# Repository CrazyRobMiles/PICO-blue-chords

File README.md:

# PICO-blue-chords

This is a chord keyboard that uses the MicroWriter chord system. It uses the Bluetooth to connect and runs on a Raspberry Pi PICO-W. It is described in the HackSpace magazine. 
## Note
This is a work in progress. The software works correctly and the PCB and the case designs are now complete but these updated designs have not been constructed. The author knows of no reason why they won't work, but he didn't know of any reasons why the prototype wouldn't work until he tried to use it...

## Using a chord keyboard
You can find instructions on how to use the keyboard and the chord shapes in the doc folder. 
## Installing the software on your PICO from the UF2 Images
You can install the software by following these steps:
1. Press down the boot button on your PICO-W.
2. Connect your PICO-W to a usb port on your computer. 
3. The PICO-W should show up as a external drive.
4. The UF2 folder holds images for left and right handed use. Drag the left or right handed uf2 file onto the drive. 
5. The PICO-W will reboot running the software.
## Printed Circuit Board Designs

The PCB designs are in the folder PICO-blue-chords-pcb. This folder also contains the partsdump.py file which can be used to extract the footprint positions for use in the case design software.
## Case 
To create a custom case design you use the PICO-blue-chords-case-builder.FCMacro macro which is in the cases folder. Load this into FreeCAD and select left or right handed and the specific key positions. The macro contains the following statements:
```
# right handed flag
right_handed = True 
if right_handed:
	keyHoles = [Little_5,Ring_5, Middle_2, Index_1, Thumb_1,Control_2]
	displayHole = Brd2
else:
      keyHoles = [Little_3,Ring_2, Middle_1, Index_2, Thumb_5,Control_5]
      displayHole = Brd1
```
Set the value of right_handed to False if you want a left-handed keyboard. Change the numbers for each key to match the position that you want for that key hole. The higher the number the farther down the keyboard the key hole will be placed. You can see the key numbers on the PCB design above. Run the macro and then export the resulting design as an STL file for printing. 
## Building the code
You use CMAKE to build the application from source. If you load the project with Visual Studio Code, make sure that you have the CMake Tools extension installed. The file CMakeLists.txt is used to create the makefiles for the build. Line 10 of this file sets the path to the SDK:
```
set(PICO_SDK_PATH "C:/Program Files/Raspberry Pi/Pico SDK v1.5.1/pico-sdk")
```
This works on my Windows system. You may need to change this when building the software on your machine. Note that you don't need to build the software yourself to use it. You can just install the image files which will be in the build folder which is created by the build process. 

## Origins

The keyboard is based on the Cykey chord design by Cy Enfield which was used as the basis of the Microwriter and Microwriter AgendA devices developed by him and Chris Rainey. You can find out more about these devices [here](http://www.computinghistory.org.uk/det/5794/Microwriter-MW4/), [here](https://www.microsoft.com/buxtoncollection/detail.aspx?id=5) and [here](https://mindmachine.co.uk/book/A/Inp-Outp/Microwriter01.html). 

If you want to buy an official Microwriter keyboard you can get one [here](https://sites.google.com/site/cykeybellaire/home). 

Have fun!

Rob Miles: [blog](https://www.robmiles.com)

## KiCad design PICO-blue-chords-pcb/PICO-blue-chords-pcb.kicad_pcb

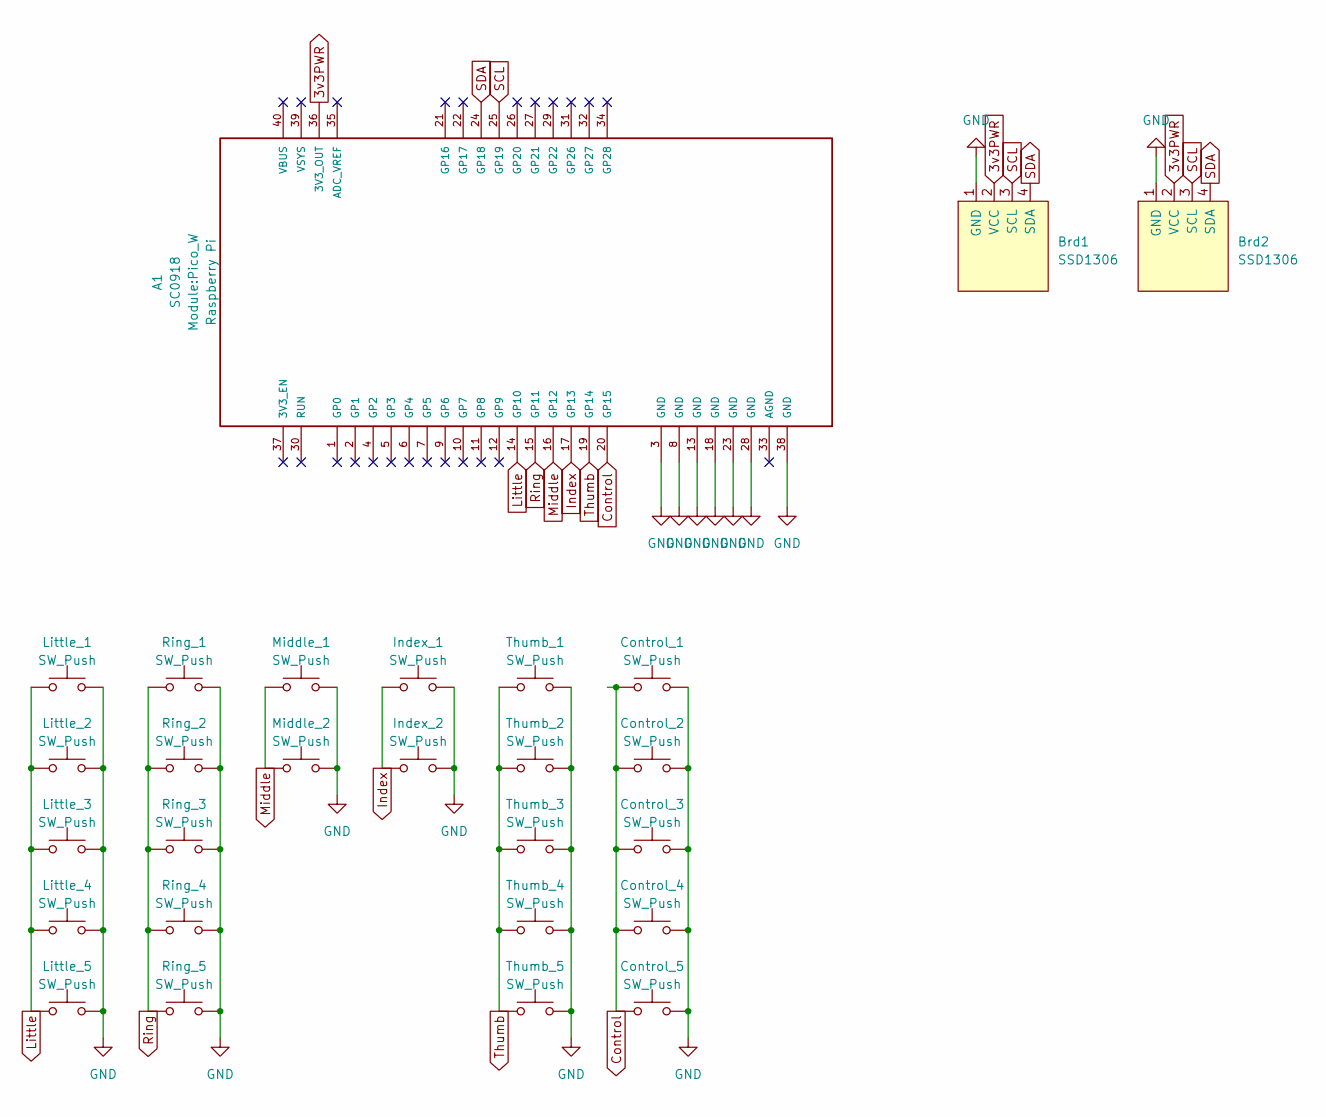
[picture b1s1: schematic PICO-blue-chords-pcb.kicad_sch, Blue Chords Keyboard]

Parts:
A1: SC0918; Pico_W; PARTREV 1.6
Brd1, Brd2: SSD1306; 128x64OLED
Control_1, Control_2, Control_3, Control_4, Control_5: SW_Push; SW_Hotswap_Kailh_MX
Index_1, Index_2: SW_Push; SW_Hotswap_Kailh_MX
Little_1, Little_2, Little_3, Little_4, Little_5: SW_Push; SW_Hotswap_Kailh_MX
Middle_1, Middle_2: SW_Push; SW_Hotswap_Kailh_MX
Ring_1, Ring_2, Ring_3, Ring_4, Ring_5: SW_Push; SW_Hotswap_Kailh_MX
Thumb_1, Thumb_2, Thumb_3, Thumb_4, Thumb_5: SW_Push; SW_Hotswap_Kailh_MX

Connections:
3v3PWR: A1.36 (3V3_OUT), Brd1.2 (VCC), Brd2.2 (VCC)
Control: A1.20 (GP15), Control_1.1, Control_2.1, Control_3.1, Control_4.1, Control_5.1
GND: A1.3 (GND), A1.8 (GND), A1.13 (GND), A1.18 (GND), A1.23 (GND), A1.28 (GND), A1.38 (GND), Brd1.1 (GND), Brd2.1 (GND), Control_1.2, Control_2.2, Control_3.2, Control_4.2, Control_5.2, Index_1.2, Index_2.2, Little_1.2, Little_2.2, Little_3.2, Little_4.2, Little_5.2, Middle_1.2, Middle_2.2, Ring_1.2, Ring_2.2, Ring_3.2, Ring_4.2, Ring_5.2, Thumb_1.2, Thumb_2.2, Thumb_3.2, Thumb_4.2, Thumb_5.2
Index: A1.17 (GP13), Index_1.1, Index_2.1
Little: A1.14 (GP10), Little_1.1, Little_2.1, Little_3.1, Little_4.1, Little_5.1
Middle: A1.16 (GP12), Middle_1.1, Middle_2.1
Ring: A1.15 (GP11), Ring_1.1, Ring_2.1, Ring_3.1, Ring_4.1, Ring_5.1
SCL: A1.25 (GP19), Brd1.3 (SCL), Brd2.3 (SCL)
SDA: A1.24 (GP18), Brd1.4 (SDA), Brd2.4 (SDA)
Thumb: A1.19 (GP14), Thumb_1.1, Thumb_2.1, Thumb_3.1, Thumb_4.1, Thumb_5.1

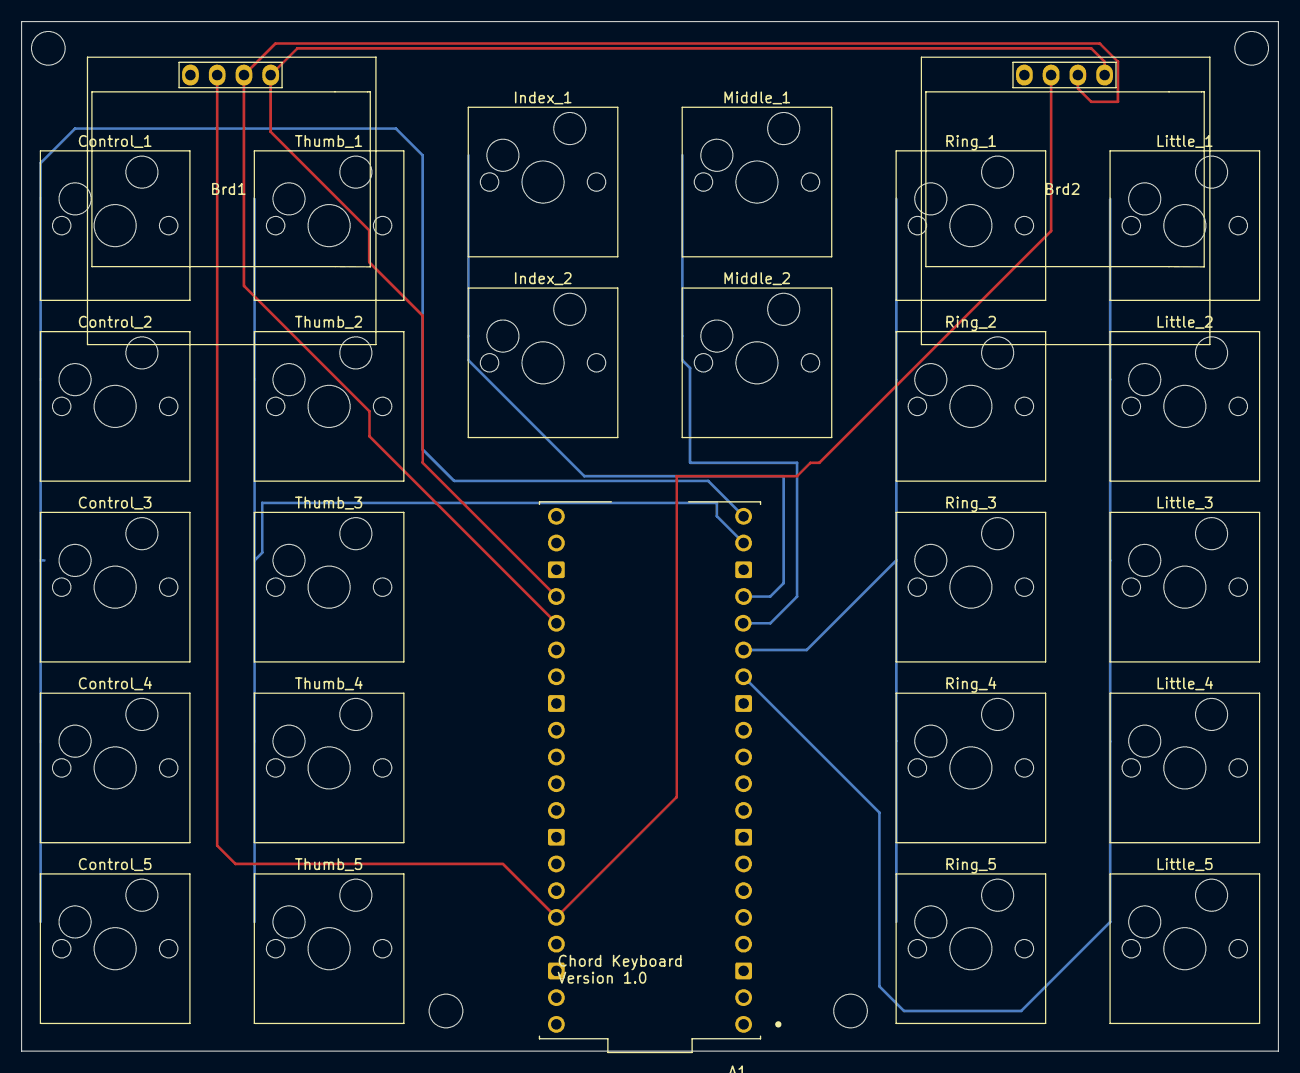
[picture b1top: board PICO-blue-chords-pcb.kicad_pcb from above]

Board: 2 copper layers, 119.4 x 97.8 mm, 27 parts (0 on the bottom side), 10 nets.

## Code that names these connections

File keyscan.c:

#include <stdio.h>
#include "pico/stdlib.h"
#include "hardware/gpio.h"
#include "messages.h"
#include "keyscan.h"

#ifdef LEFT_HANDED_KEYBOARD

#define LITTLE_KEY_GPIO 15
#define RING_KEY_GPIO 14
#define MIDDLE_KEY_GPIO 13
#define INDEX_KEY_GPIO 12
#define THUMB_KEY_GPIO 11
#define CONTROL_KEY_GPIO 10

#else

#define LITTLE_KEY_GPIO 10
#define RING_KEY_GPIO 11
#define MIDDLE_KEY_GPIO 12
#define INDEX_KEY_GPIO 13
#define THUMB_KEY_GPIO 14
#define CONTROL_KEY_GPIO 15

#endif

enum keyboard_states
{
    UPPER_CASE_KEYS,
    LOWER_CASE_KEYS,
    NUMBER_KEYS,
    SYMBOL_KEYS
};

enum keyboard_states keyboard_state;

struct key
{
    int gpio;
    bool state;
    char *name;
    int change_counter;
    int bit_number;
};

struct key keys[] =
    {
        {LITTLE_KEY_GPIO, false, "little key", 0, 0},
        {RING_KEY_GPIO, false, "ring key", 0, 1},
        {MIDDLE_KEY_GPIO, false, "middle key", 0, 2},
        {INDEX_KEY_GPIO, false, "index key", 0, 3},
        {THUMB_KEY_GPIO, false, "thumb", 0, 4},
        {CONTROL_KEY_GPIO, false, "control", 0, 5}};

#define DEBOUNCE_COUNT 1
#define KEY_PRESSED false

struct key_decode
{
    int scan;
    char ch;
};

struct key_decode lower_case_text_decode[] = {
    {12, 'a'},
    {56, 'b'},
    {10, 'c'},
    {14, 'd'},
    {4, 'e'},
    {30, 'f'},
    {48, 'g'},
    {34, 'h'},
    {6, 'i'},
    {50, 'j'},
    {18, 'k'},
    {38, 'l'},
    {60, 'm'},
    {24, 'n'},
    {8, 'o'},
    {62, 'p'},
    {40, 'q'},
    {22, 'r'},
    {16, 's'},
    {20, 't'},
    {32, 'u'},
    {36, 'v'},
    {54, 'w'},
    {58, 'x'},
    {26, 'y'},
    {42, 'z'},
    {2, ' '},
    {52, ','},
    {28, '.'},
    {0, ' '}};

struct key_decode upper_case_text_decode[] = {
    {12, 'A'},
    {56, 'B'},
    {10, 'C'},
    {14, 'D'},
    {4, 'E'},
    {30, 'F'},
    {48, 'G'},
    {34, 'H'},
    {6, 'I'},
    {50, 'J'},
    {18, 'K'},
    {38, 'L'},
    {60, 'M'},
    {24, 'N'},
    {8, 'O'},
    {62, 'P'},
    {40, 'Q'},
    {22, 'R'},
    {16, 'S'},
    {20, 'T'},
    {32, 'U'},
    {36, 'V'},
    {54, 'W'},
    {58, 'X'},
    {26, 'Y'},
    {42, 'Z'},
    {2, ' '},
    {52, ','},
    {28, '.'},
    {0, ' '}};

struct key_decode num_decode[] = {
    {8, '0'},
    {2, '1'},
    {6, '2'},
    {14, '3'},
    {30, '4'},
    {62, '5'},
    {32, '6'},
    {48, '7'},
    {56, '8'},
    {60, '9'},
    {52, '}'},
    {28, '.'},
    {0, ' '}};

struct key_decode sym_decode[] = {
    {2, ' '},
    {52, ','},
    {28, '.'},
    {54, ','},
    {50, ';'},
    {42, '%'},
    {4, '='},
    {22, '&'},
    {14, '('},
    {56, ')'},
    {16, '$'},
    {12, '@'},
    {62, '+'},
    {34, '#'},
    {24, '-'},
    {58, '!'},
    {26, '?'},
    {18, '/'},
    {30, '{'},
    {60, '}'},
    {10, '['},
    {40, ']'},
    {36, '\\'},
    {20, '*'},
    {6, '<'},
    {48, '>'},
    {0, ' '}};

char find_char(char scan, struct key_decode *decode)
{
    while (decode->scan > 0)
    {
        if (scan == decode->scan)
        {
            return decode->ch;
        }
        decode++;
    }
    // return 0 if we reach the end without finding a character
    return 0;
}

char key_bits = 0;
char assembling_bits = false;

int poll_gpio()
{
    char result = 0;

    for (int i = 0; i < sizeof(keys) / sizeof(struct key); i++)
    {

        int bit_mask = 1 << keys[i].bit_number;
        int gpio = keys[i].gpio;
        int in_state = gpio_get(gpio);
        if (keys[i].state == in_state)
        {
            keys[i].change_counter = 0;
        }
        else
        {
            keys[i].change_counter++;
            if (keys[i].change_counter >= DEBOUNCE_COUNT)
            {
                // Got a proper key state change
                // clear the debounce counter
                keys[i].change_counter = 0;
                keys[i].state = in_state;
                if (in_state == KEY_PRESSED)
                {
                    // key has been pressed
                    if (key_bits == 0)
                    {
                        // first press of a key
                        assembling_bits = true;
                    }
                    key_bits = key_bits + bit_mask;
                }
                else
                {
                    // key has been released
                    int bits = key_bits;
                    key_bits = key_bits - bit_mask;
                    if (assembling_bits)
                    {
                        // first key lifted which is part of a character
                        // decode it
                        result = bits;
                        assembling_bits = false;
                    }
                }
            }
        }
    }
    return result;
}

bool old_state;

void set_keyboard_state(enum keyboard_states state)
{

    keyboard_state = state;

    switch (keyboard_state)
    {
    case UPPER_CASE_KEYS:
        display_shift_status("CAPS");
        break;
    case LOWER_CASE_KEYS:
        display_shift_status("lower");
        break;
    case NUMBER_KEYS:
        display_shift_status("NUMB");
        break;
    case SYMBOL_KEYS:
        display_shift_status("SYM");
        break;
    }
}

void toggle_caps_lock()
{
    if (keyboard_state == UPPER_CASE_KEYS)
    {
        set_keyboard_state(LOWER_CASE_KEYS);
    }
    else
    {
        if (keyboard_state == LOWER_CASE_KEYS)
        {
            set_keyboard_state(UPPER_CASE_KEYS);
        }
    }
}

#define CHAR_RETURN '\n'
#define CHAR_ESCAPE 27
#define CHAR_TAB '\t'
#define CHAR_BACKSPACE 0x7f

int scan_keys()
{
    int bits = poll_gpio();

    if (bits == 0)
    {
        return 0;
    }

    char ch = 0;

    // decode the bits into a character
    switch (keyboard_state)
    {
    case UPPER_CASE_KEYS:
        ch = find_char(bits, upper_case_text_decode);
        break;
    case LOWER_CASE_KEYS:
        ch = find_char(bits, lower_case_text_decode);
        break;
    case NUMBER_KEYS:
        ch = find_char(bits, num_decode);
        break;
    case SYMBOL_KEYS:
        ch = find_char(bits, sym_decode);
        break;
    }

    if (ch == 0)
    {
        switch (bits)
        {
        case 1:
            toggle_caps_lock();
            break;
        case 13:
            ch = CHAR_BACKSPACE;
            break;
        case 17:
            set_keyboard_state(SYMBOL_KEYS);
            break;
        case 21:
            set_keyboard_state(LOWER_CASE_KEYS);
            break;
        case 25:
            set_keyboard_state(NUMBER_KEYS);
            break;
        case 44:
            ch = CHAR_RETURN;
            break;
        }
    }

    add_character_to_message(ch);

    return ch;
}

int init_keyscan()
{
    printf("starting keyscan");

    for (int i = 0; i < sizeof(keys) / sizeof(struct key); i++)
    {
        int bit_mask = 1 << keys[i].bit_number;
        int gpio = keys[i].gpio;
        gpio_set_dir(i, gpio);
        gpio_pull_up(gpio);
        int in_state = gpio_get(i);
        keys[i].state = in_state;
        if (in_state == KEY_PRESSED)
        {
            key_bits = key_bits + bit_mask;
        }
    }

    clear_message();

    set_keyboard_state(LOWER_CASE_KEYS);

    return 0;
}

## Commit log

2023-05-19 Version 1.0
2023-05-24 Some small layout changes
2023-05-25 Alpha release
2023-06-16 Upgraded to use SDK and added missing PCB tracks.
2023-06-16 Feature complete release
